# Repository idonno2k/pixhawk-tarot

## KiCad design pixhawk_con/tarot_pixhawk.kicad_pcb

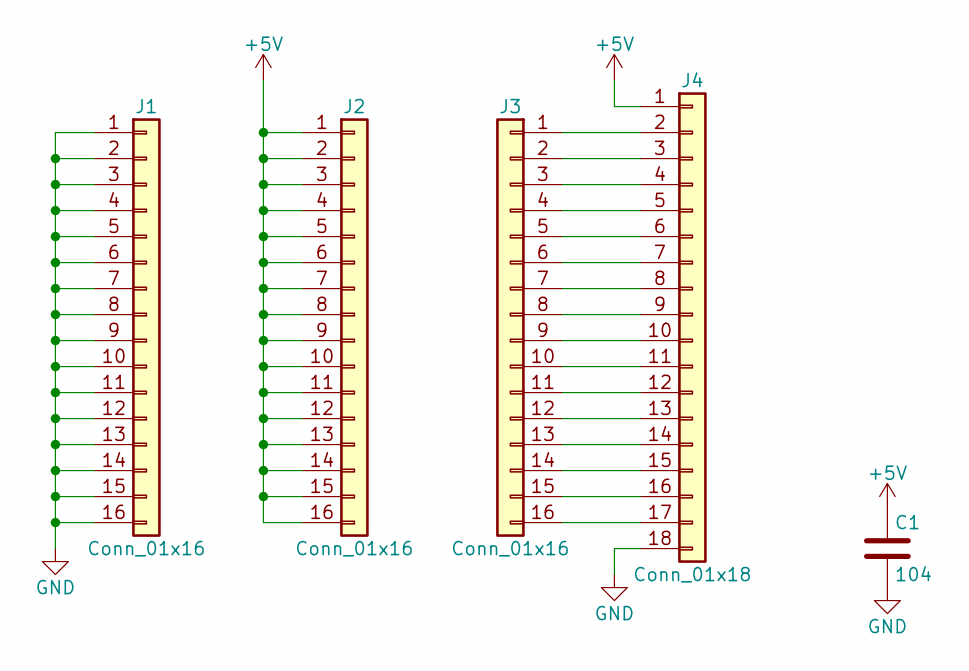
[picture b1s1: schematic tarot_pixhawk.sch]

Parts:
C1: 104; C_1206
J1, J2, J3: Conn_01x16; Pin_Header_Straight_1x16_Pitch2.54mm
J4: Conn_01x18; Pin_Header_Straight_1x18_Pitch2.54mm

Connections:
+5V: C1.1, J2.1, J2.2, J2.3, J2.4, J2.5, J2.6, J2.7, J2.8, J2.9, J2.10, J2.11, J2.12, J2.13, J2.14, J2.15, J2.16, J4.1
GND: C1.2, J1.1, J1.2, J1.3, J1.4, J1.5, J1.6, J1.7, J1.8, J1.9, J1.10, J1.11, J1.12, J1.13, J1.14, J1.15, J1.16, J4.18
unnamed: J3.1, J4.2
unnamed: J3.2, J4.3
unnamed: J3.3, J4.4
unnamed: J3.4, J4.5
unnamed: J3.5, J4.6
unnamed: J3.6, J4.7
unnamed: J3.7, J4.8
unnamed: J3.8, J4.9
unnamed: J3.9, J4.10
unnamed: J3.10, J4.11
unnamed: J3.11, J4.12
unnamed: J3.12, J4.13
unnamed: J3.13, J4.14
unnamed: J3.14, J4.15
unnamed: J3.15, J4.16
unnamed: J3.16, J4.17

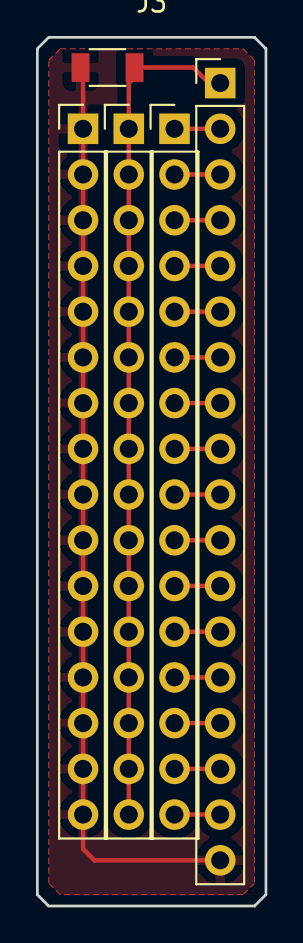
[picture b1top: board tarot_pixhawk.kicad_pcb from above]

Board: 2 copper layers, 12.7 x 48.3 mm, 5 parts (0 on the bottom side), 18 nets.

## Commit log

2020-03-03 pixhawk 커넥터보드
2020-03-06 shield
2020-03-08 no message
